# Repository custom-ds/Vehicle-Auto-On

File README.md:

# Vehicle Auto-On #

## Source ##

### Configuring the Dev Environment ###
Install Platform IO in Visual Studio Code

Use the jtag2updi

https://dev.to/dariocasciato/attiny85-programming-your-complete-guide-with-arduino-and-platformio-37do

https://www.electronics-lab.com/project/programming-attiny10-platform-io-ide/

### Programming ###

With the Arduion programmer board loaded with the jtag2updi software, and the Pin 6 from the Arduino connected to the Reset
line on the ATTiny404, you can Build and Program directly inside of the Visual Studio Code.

To build, go to the bottom-left part of the screen to the Status Bar area of VSCode, and there should be some little icons
that Platform IO installed. The Checkmark icon is the Build option, and will compile/build the code that is written.

Once it compiles successfully, there is a second icon that is a right-arrow to click, which will utilize the Arduino
programmer to program the ATTiny via UPDI.

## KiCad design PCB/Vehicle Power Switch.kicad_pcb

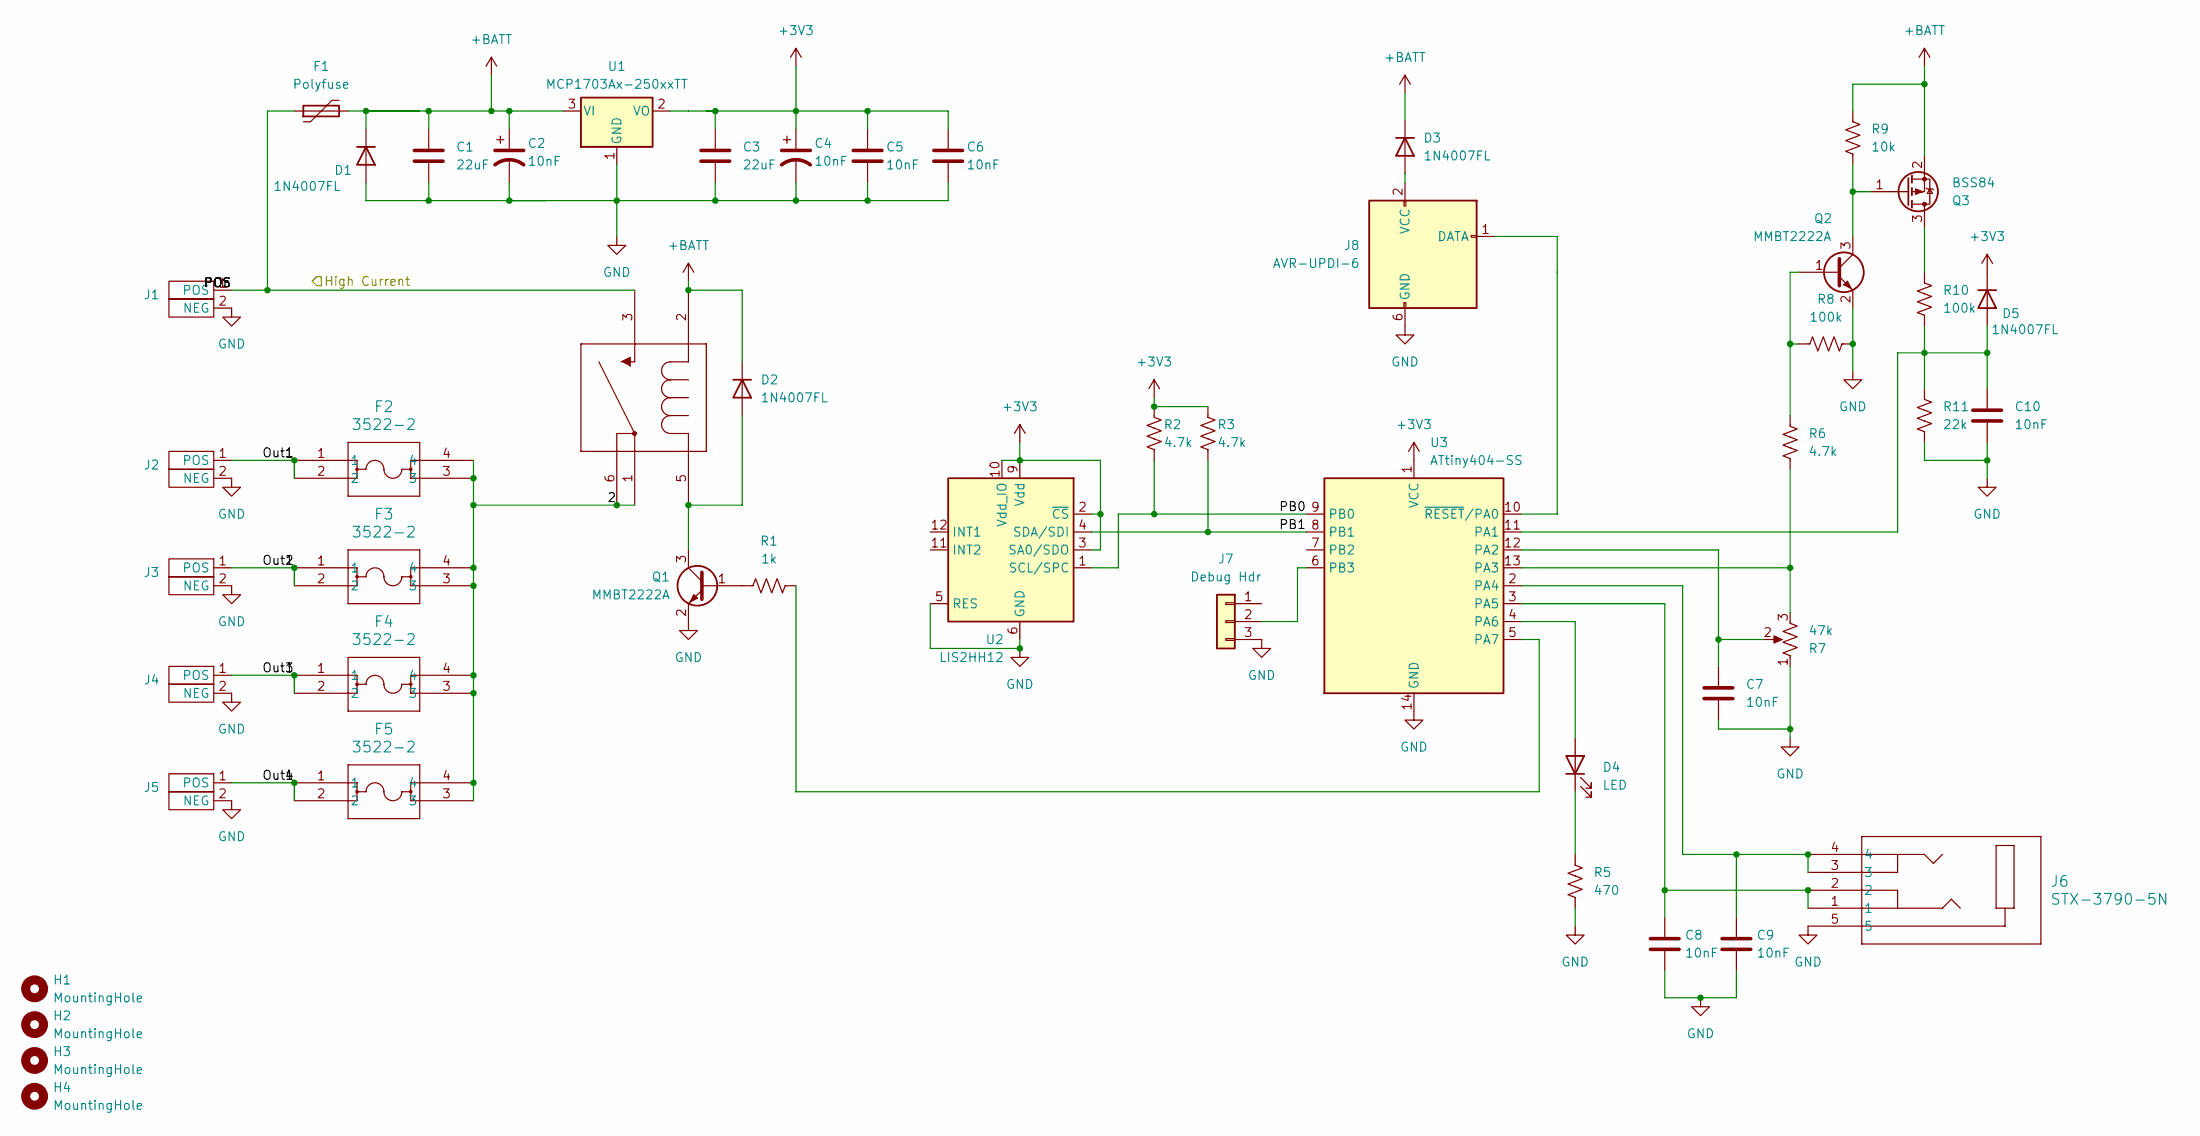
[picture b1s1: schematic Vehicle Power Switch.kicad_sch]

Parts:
C1, C3: 22uF; C_0805_2012Metric; Digikey 13-CC0805MFX5R8BB226CT-ND
C2, C4, C5, C6, C7, C8, C9, C10: 10nF; C_0805_2012Metric; Digikey 399-1158-1-ND
D1, D2, D3, D5: 1N4007FL; D_SOD-123; Digikey 1655-1N4007FLCT-ND
D4: LED; LED_0805_2012Metric
F1: Polyfuse; Fuse_1206_3216Metric; Digikey 507-1794-1-ND
F2, F3, F4, F5: 3522-2; Fuse Clip Blade - 3522-2; Digikey 36-3522-2-ND
H1, H2, H3, H4: MountingHole; MountingHole_3.2mm_M3_ISO14580_Pad
J1, J2, J3, J4, J5: Anderson Powerpole Vertical
J6: STX-3790-5N; Stereo Jack Vertical - STX-3790-5N; Digikey 2092-STX-3790-5N-ND
J7: Debug Hdr; PinSocket_1x03_P2.54mm_Vertical
J8: AVR-UPDI-6; IDC-Header_2x03_P2.54mm_Vertical
K1: 12V Relay - ACNH; Digikey 255-2583-ND
Q1, Q2: MMBT2222A; SOT-23; Digikey 4878-MMBT2222ATR-ND
Q3: BSS84; SOT-23; Digikey BSS84CT-ND
R1: 1k; R_0805_2012Metric
R2, R3, R6: 4.7k; R_0805_2012Metric
R5: 470; R_0805_2012Metric
R7: 47k; Potentiometer_Bourns_3386P_Vertical; Digikey 3386P-1-473LF-ND
R8, R10: 100k; R_0805_2012Metric
R9: 10k; R_0805_2012Metric
R11: 22k; R_0805_2012Metric
U1: MCP1703Ax-250xxTT; TSOT-23; Digikey MCP1703AT-3302E/CB
U2: LIS2HH12; LGA-12_2x2mm_P0.5mm; Digikey 497-15069-1-ND
U3: ATtiny404-SS; SOIC-14_3.9x8.7mm_P1.27mm; Digikey ATTINY404-SSFRTR-ND

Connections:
+3V3: C3.1, C4.1, C5.1, C6.1, D5.1 (K), R2.1, R3.1, U1.2 (VO), U2.2 (~CS), U2.3 (SA0/SDO), U2.9 (Vdd), U2.10 (Vdd_IO), U3.1 (VCC)
+BATT: C1.1, C2.1, D1.1 (K), D2.1 (K), D3.1 (K), F1.2, K1.2 (5), Q3.2 (S), R9.1, U1.3 (VI)
/1: F2.1, F2.2, F3.1, F3.2, F4.1, F4.2, F5.1, F5.2, J2.1 (POS), J3.1 (POS), J4.1 (POS), J5.1 (POS)
/2: F2.3, F2.4, F3.3, F3.4, F4.3, F4.4, F5.3, F5.4, K1.1 (4), K1.6 (2)
/In: F1.1, J1.1 (POS), K1.3
/PB0: R2.2, U2.1 (SCL/SPC), U3.9 (PB0)
/PB1: R3.2, U2.4 (SDA/SDI), U3.8 (PB1)
GND: C1.2, C2.2, C3.2, C4.2, C5.2, C6.2, C7.2, C8.2, C9.2, C10.2, D1.2 (A), J1.2 (NEG), J2.2 (NEG), J3.2 (NEG), J4.2 (NEG), J5.2 (NEG), J6.5, J7.3, J8.6 (GND), Q1.2 (E), Q2.2 (E), R5.2, R7.1, R8.2, R11.2, U1.1 (GND), U2.5 (RES), U2.6 (GND), U2.7 (GND), U2.8 (GND), U3.14 (GND)
unnamed: D2.2 (A), K1.5 (1), Q1.3 (C)
unnamed: D3.2 (A), J8.2 (VCC)
unnamed: D4.2 (A), U3.4 (PA6)
unnamed: D4.1 (K), R5.1
unnamed: C10.1, D5.2 (A), R10.2, R11.1, U3.11 (PA1)
unnamed: J7.2, U3.6 (PB3)
unnamed: J8.1 (DATA), U3.10 (~RESET/PA0)
unnamed: Q1.1 (B), R1.1
unnamed: Q2.1 (B), R6.1, R8.1
unnamed: Q2.3 (C), Q3.1 (G), R9.2
unnamed: Q3.3 (D), R10.1
unnamed: C7.1, R7.2, U3.12 (PA2)
unnamed: R6.2, R7.3, U3.13 (PA3)
unnamed: C9.1, J6.3, J6.4, U3.2 (PA4)
unnamed: C8.1, J6.1, J6.2, U3.3 (PA5)
unnamed: R1.2, U3.5 (PA7)

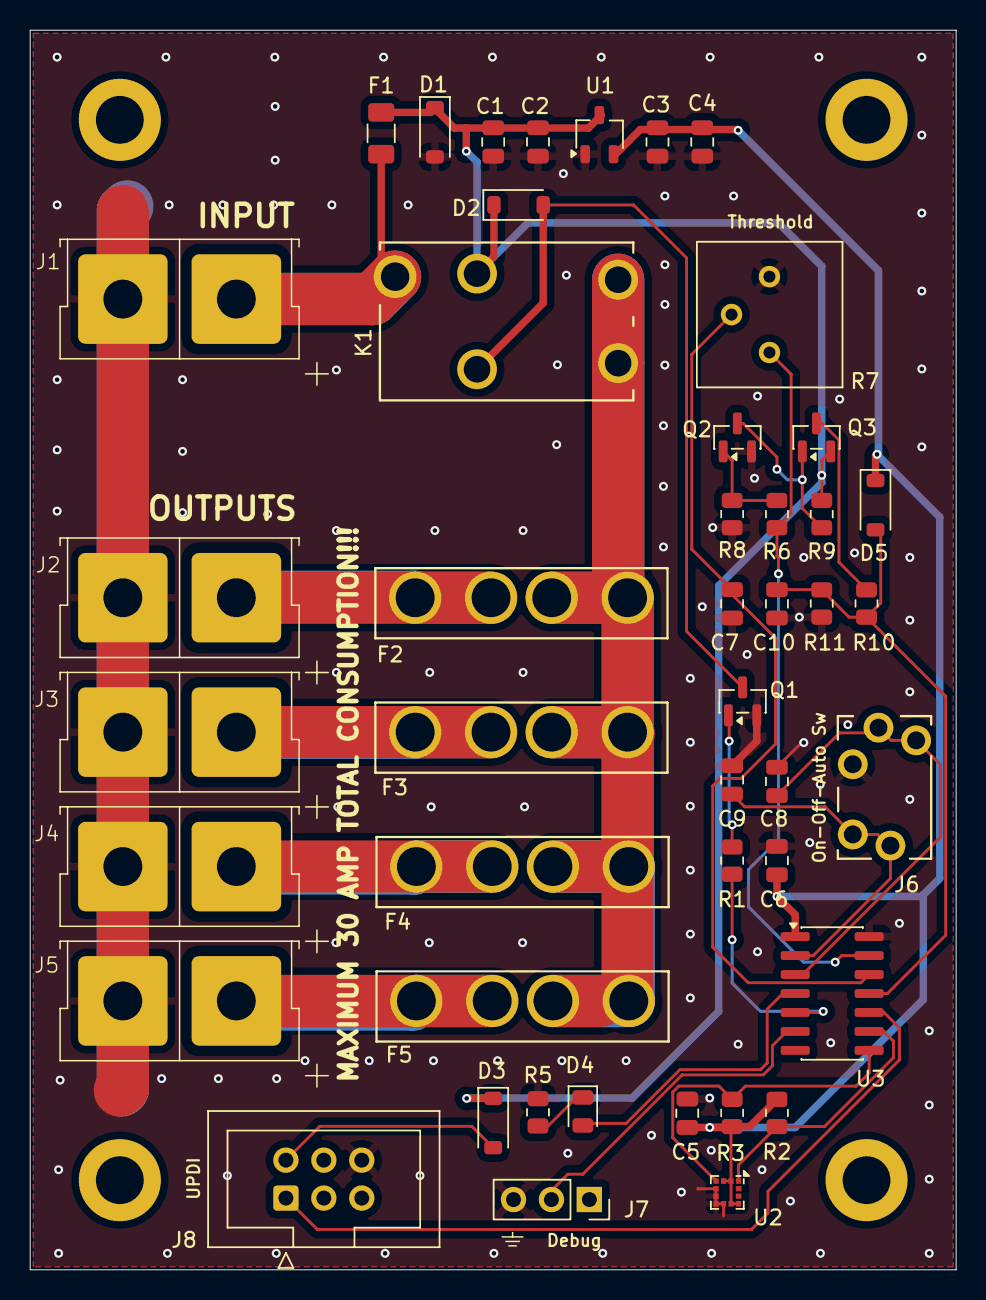
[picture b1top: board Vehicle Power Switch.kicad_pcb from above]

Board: 2 copper layers, 62.0 x 83.0 mm, 49 parts (0 on the bottom side), 24 nets.

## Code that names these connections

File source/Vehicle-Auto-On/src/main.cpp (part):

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

//Outputs
#define LED_STATUS PIN_PA6
#define ANALOG_ENABLE PIN_PA3
#define RELAY PIN_PA7


//Digital Inputs
#define SWITCH_AUTO PIN_PA4
#define SWITCH_ON PIN_PA5

//Analog Inputs
#define ANALOG_BATTERY_LEVEL PIN_PA1
#define ANALOG_REFERENCE PIN_PA2

//Software Serial pins
#define DEBUG_SERIAL
#define SOFT_SERIAL_TX PIN_PB3

//Constants
#define SWITCH_POSITION_DELAY 3
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  pinMode(ANALOG_REFERENCE, INPUT);


  // Initialize custom bit-banged serial on PB2 (TX) and PB3 (RX)
  // Use a lower baud rate for better reliability with ATtiny404 at 3.33MHz
  customSerialInit();  // Initialize custom serial at 1200 baud

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
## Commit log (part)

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2024-06-24 Initial Commit
    PCB version 2.0 is done. Source is stubbed in.
2025-10-06 Fixes to PCB v2 and working on firmware.
2025-12-15 All functionality is working on the prototype. Firmware is still rough.
2025-12-16 Low power testing showing 100uA during low power loop.
2025-12-19 Firmware approaching release candidate.
2026-03-10 Release candidate for firmware.
2026-04-03 Added option for case top with no penetrations (for simple power-strip functionality)
